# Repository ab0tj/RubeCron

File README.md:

This is just a goofy SBC I created for myself that is also a binary clock.
I have made it public in case it is helpful to anyone else, but it isn't intended to be finished product by any means.

That said, it works for me but YMMV.

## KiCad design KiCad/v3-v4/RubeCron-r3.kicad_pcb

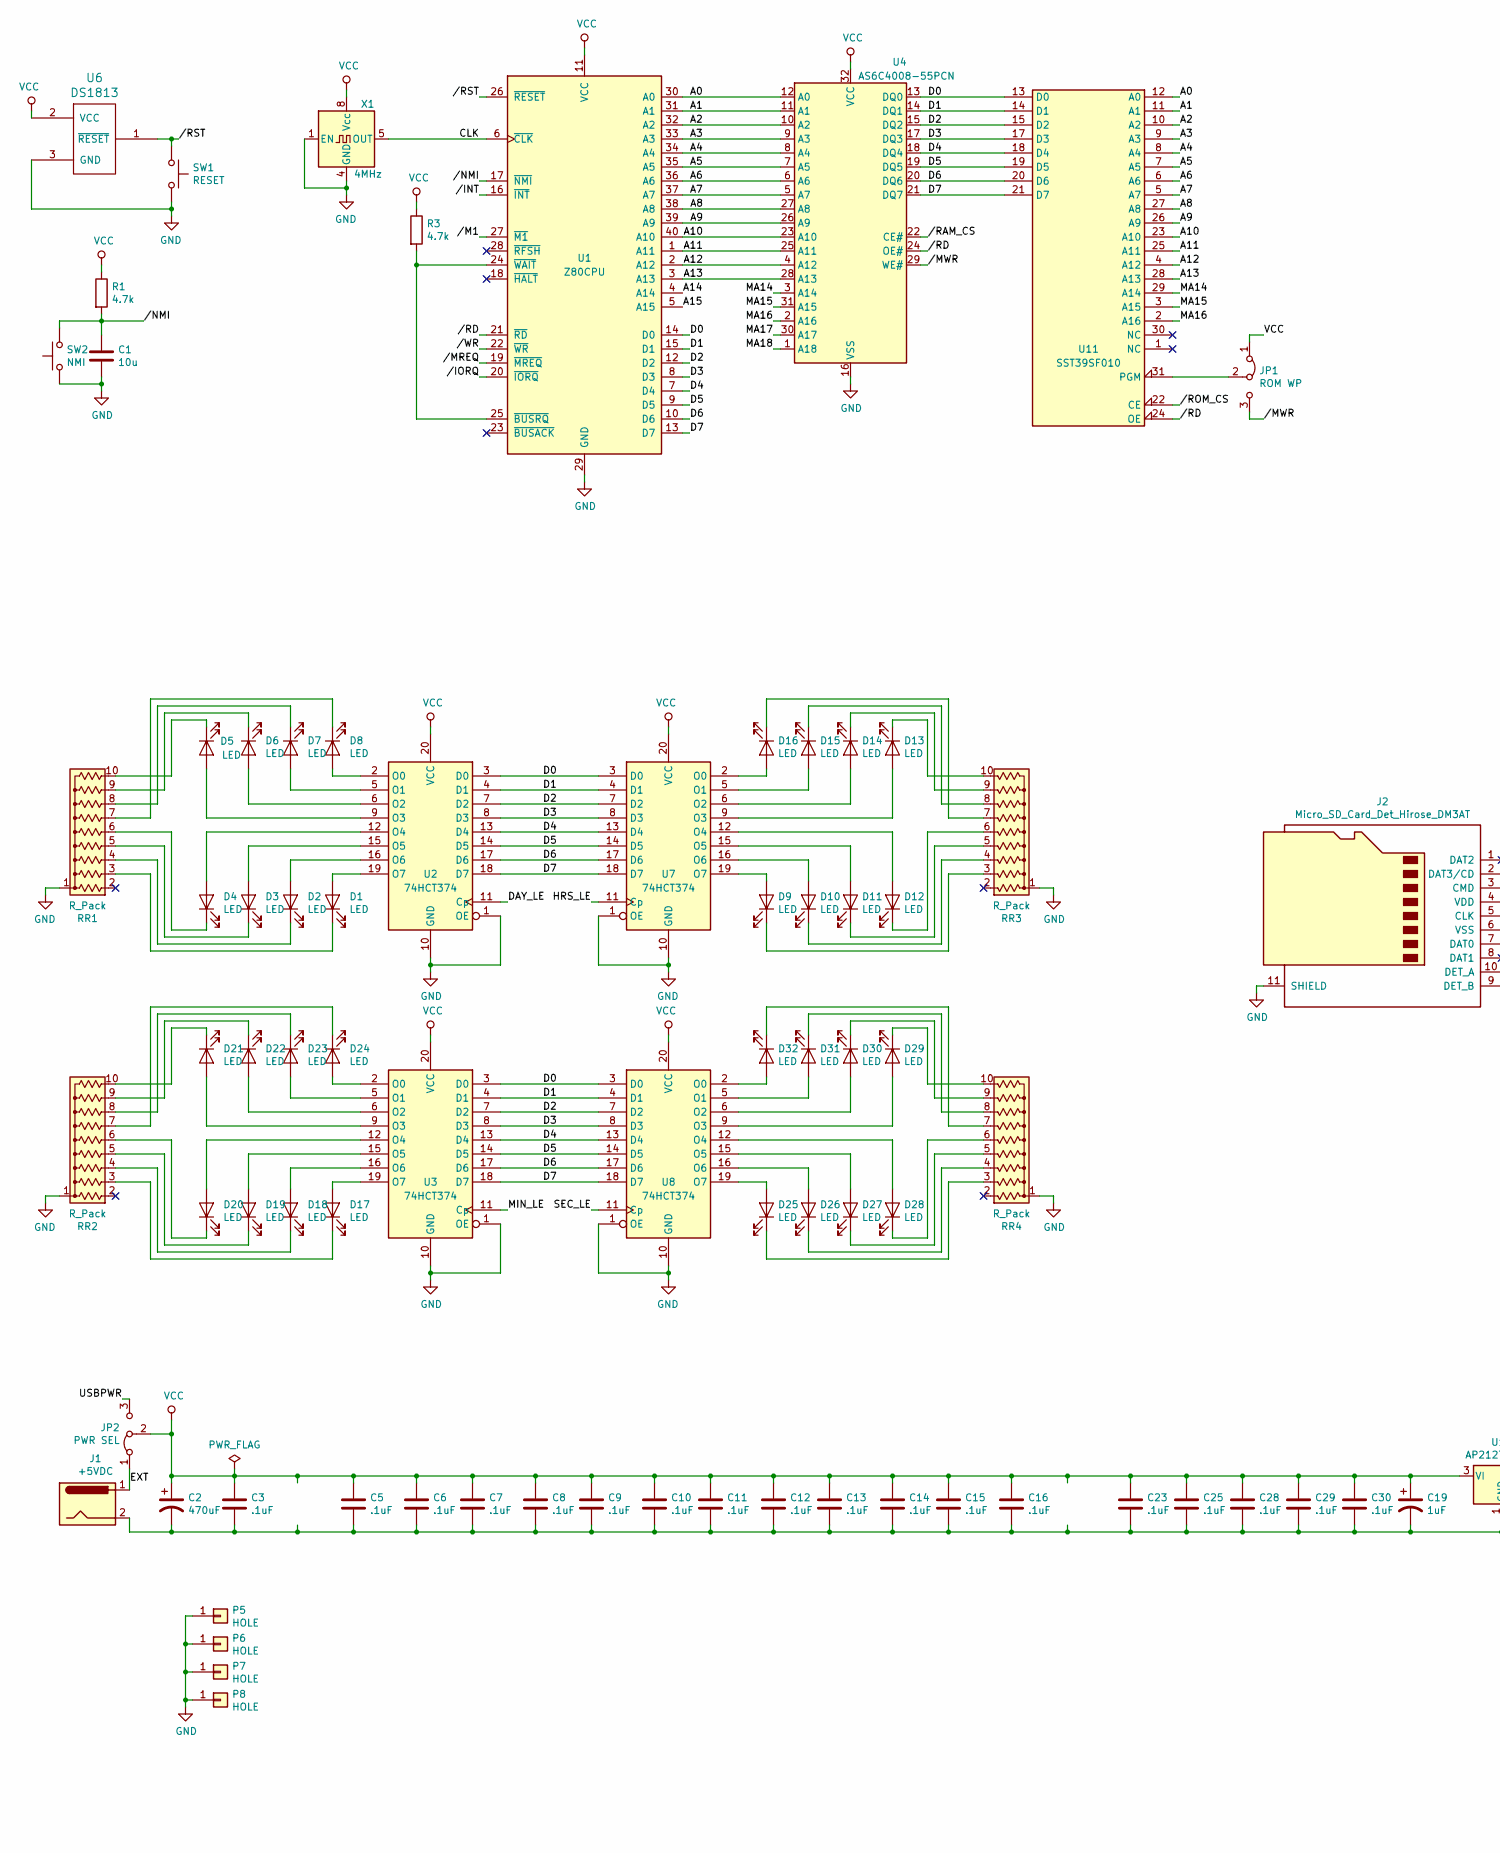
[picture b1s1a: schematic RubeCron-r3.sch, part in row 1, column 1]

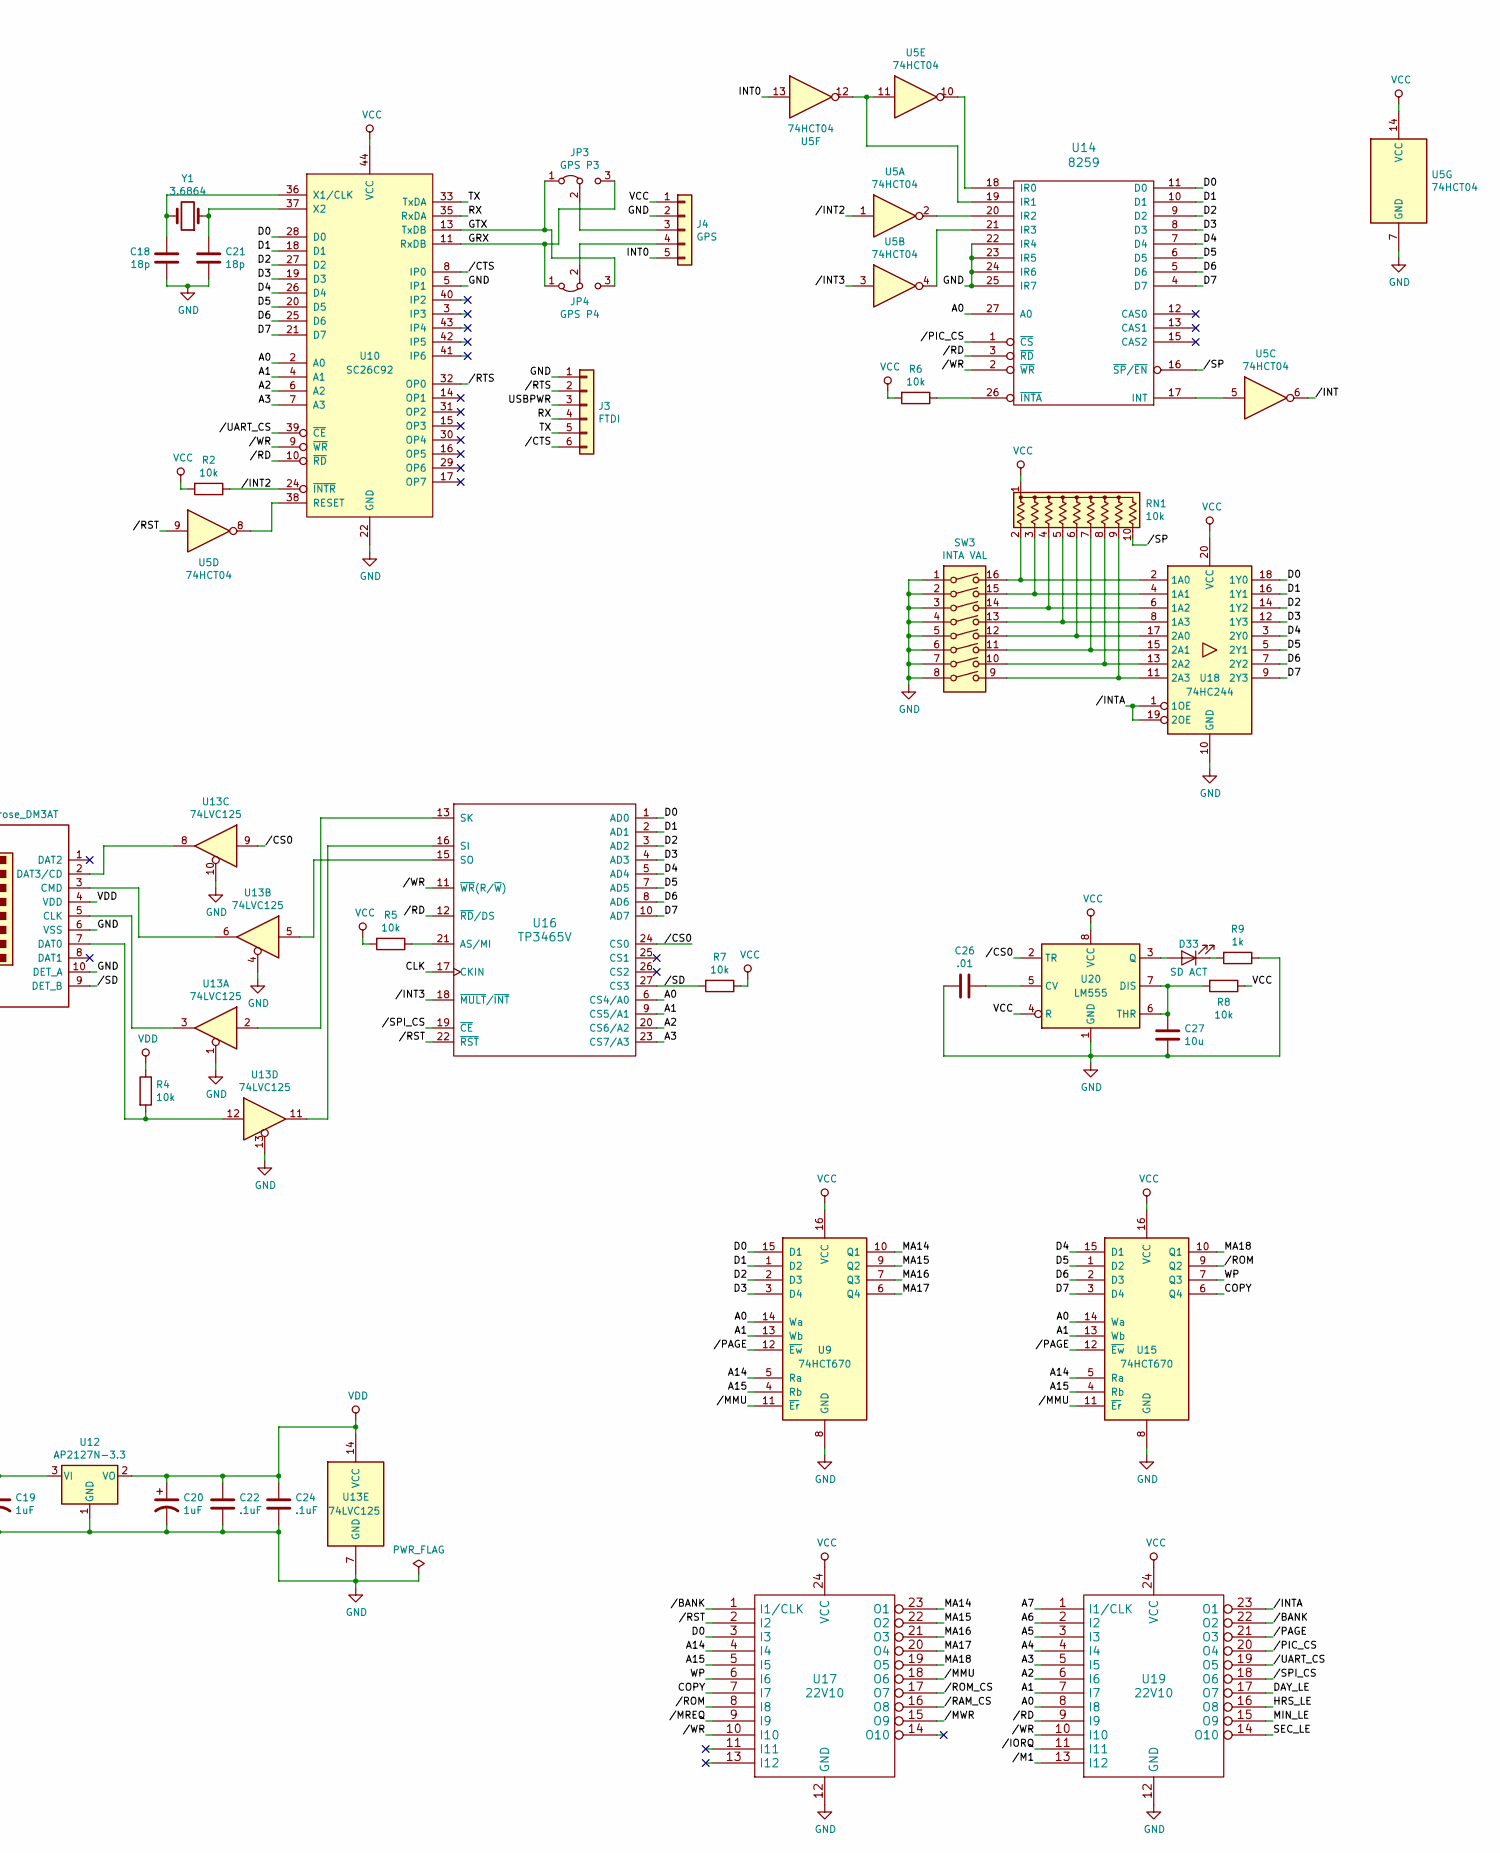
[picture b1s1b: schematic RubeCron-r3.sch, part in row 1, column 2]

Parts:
C1, C27: 10u; C_Disc_D5.0mm_W2.5mm_P5.00mm
C2: 470uF; CP_Radial_D8.0mm_P3.50mm
C3, C5, C6, C7, C8, C9, C10, C11, C12, C13, C14, C15, C16, C23, C25, C28, C29, C30: .1uF; C_Disc_D5.0mm_W2.5mm_P5.00mm
C18, C21: 18p; C_Disc_D5.0mm_W2.5mm_P5.00mm
C19, C20: 1uF; C_0805_2012Metric_Pad1.15x1.40mm_HandSolder
C22, C24: .1uF; C_0805_2012Metric_Pad1.15x1.40mm_HandSolder
C26: .01; C_Disc_D5.0mm_W2.5mm_P5.00mm
D1, D2, D3, D4, D5, D6, D7, D8, D9, D10, D11, D12, D13, D14, D15, D16, D17, D18, D19, D20, D21, D22, D23, D24, D25, D26, D27, D28, D29, D30, D31, D32: LED; LED_D5.0mm
D33: SD ACT; LED_D3.0mm
J1: +5VDC; BarrelJack_CUI_PJ-102AH_Horizontal
J2: Micro_SD_Card_Det_Hirose_DM3AT; microSD_HC_Hirose_DM3AT-SF-PEJM5
J3: FTDI; PinHeader_1x06_P2.54mm_Horizontal
J4: GPS; PinSocket_1x05_P2.54mm_Vertical
JP1: ROM WP; PinHeader_1x03_P2.54mm_Vertical
JP2: PWR SEL; PinHeader_1x03_P2.54mm_Vertical
JP3: GPS P3; SolderJumper-3_P1.3mm_Open_Pad1.0x1.5mm
JP4: GPS P4; SolderJumper-3_P1.3mm_Open_Pad1.0x1.5mm
P5, P6, P7, P8: HOLE; MountingHole_3mm_Pad
R1, R3: 4.7k; R_Axial_DIN0207_L6.3mm_D2.5mm_P7.62mm_Horizontal
R2, R5, R6, R7, R8: 10k; R_Axial_DIN0207_L6.3mm_D2.5mm_P7.62mm_Horizontal
R4: 10k; R_0805_2012Metric_Pad1.15x1.40mm_HandSolder
R9: 1k; R_Axial_DIN0207_L6.3mm_D2.5mm_P7.62mm_Horizontal
RN1: 10k; R_Array_SIP10
RR1, RR2, RR3, RR4: R_Pack; R_Array_SIP10
SW1: RESET; SW_PUSH_6mm
SW2: NMI; SW_PUSH_6mm
SW3: INTA VAL; SW_DIP_SPSTx08_Slide_9.78x22.5mm_W7.62mm_P2.54mm
U1: Z80CPU; DIP-40_W15.24mm_Socket
U2, U3, U7, U8: 74HCT374; DIP-20_W7.62mm_Socket
U4: AS6C4008-55PCN; DIP-32_W15.24mm_Socket
U5: 74HCT04; DIP-14_W7.62mm_Socket
U6: DS1813; TO-92L_Inline
U9, U15: 74HCT670; DIP-16_W7.62mm_Socket
U10: SC26C92; PLCC-44_THT-Socket
U11: SST39SF010; DIP-32_W15.24mm_Socket
U12: AP2127N-3.3; SOT-23
U13: 74LVC125; SOIC-14_3.9x8.7mm_P1.27mm
U14: 8259; PLCC-28_THT-Socket
U16: TP3465V; PLCC-28_THT-Socket
U17, U19: 22V10; DIP-24_W7.62mm_Socket
U18: 74HC244; DIP-20_W7.62mm_Socket
U20: LM555; DIP-8_W7.62mm_Socket
X1: 4MHz; Oscillator_DIP-8
Y1: 3.6864; Crystal_HC49-U_Vertical

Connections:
//BANK: U17.1 (I1/CLK), U19.22 (O2)
//CS0: U13.9, U16.24 (CS0), U20.2 (TR)
//CTS: J3.6, U10.8 (IP0)
//INT: U1.16 (~INT~), U5.6
//INT2: R2.1, U5.1, U10.24 (~INTR)
//INT3: U5.3, U16.18 (~MULT~/~INT)
//INTA: U18.1 (1OE), U18.19 (2OE), U19.23 (O1)
//IORQ: U1.20 (~IORQ~), U19.11 (I11)
//M1: U1.27 (~M1~), U19.13 (I12)
//MMU: U9.11 (~Er), U15.11 (~Er), U17.18 (O6)
//MREQ: U1.19 (~MREQ~), U17.9 (I9)
//MWR: JP1.3 (B), U4.29 (WE#), U17.15 (O9)
//NMI: C1.1, R1.2, SW2.2, U1.17 (~NMI~)
//PAGE: U9.12 (~Ew), U15.12 (~Ew), U19.21 (O3)
//PIC_CS: U14.1 (~CS), U19.20 (O4)
//RAM_CS: U4.22 (CE#), U17.16 (O8)
//RD: U1.21 (~RD~), U4.24 (OE#), U10.10 (~RD), U11.24 (OE), U14.3 (~RD), U16.12 (~RD~/DS), U19.9 (I9)
//ROM: U15.9 (Q2), U17.8 (I8)
//ROM_CS: U11.22 (CE), U17.17 (O7)
//RST: SW1.2, U1.26 (~RESET~), U5.9, U6.1 (~RESET), U16.22 (~RST), U17.2 (I2)
//RTS: J3.2, U10.32 (OP0)
//SD: J2.9 (DET_B), R7.2, U16.27 (CS3)
//SP: RN1.10 (R9), U14.16 (~SP~/~EN~)
//SPI_CS: U16.19 (~CE), U19.18 (O6)
//UART_CS: U10.39 (~CE), U19.19 (O5)
//WR: U1.22 (~WR~), U10.9 (~WR), U14.2 (~WR), U16.11 (~WR~(R/~W~)), U17.10 (I10), U19.10 (I10)
/A0: U1.30 (A0), U4.12 (A0), U9.14 (Wa), U10.2 (A0), U11.12 (A0), U14.27 (A0), U15.14 (Wa), U16.6 (CS4/A0), U19.8 (I8)
/A1: U1.31 (A1), U4.11 (A1), U9.13 (Wb), U10.4 (A1), U11.11 (A1), U15.13 (Wb), U16.9 (CS5/A1), U19.7 (I7)
/A2: U1.32 (A2), U4.10 (A2), U10.6 (A2), U11.10 (A2), U16.20 (CS6/A2), U19.6 (I6)
/A3: U1.33 (A3), U4.9 (A3), U10.7 (A3), U11.9 (A3), U16.23 (CS7/A3), U19.5 (I5)
/A4: U1.34 (A4), U4.8 (A4), U11.8 (A4), U19.4 (I4)
/A5: U1.35 (A5), U4.7 (A5), U11.7 (A5), U19.3 (I3)
/A6: U1.36 (A6), U4.6 (A6), U11.6 (A6), U19.2 (I2)
/A7: U1.37 (A7), U4.5 (A7), U11.5 (A7), U19.1 (I1/CLK)
/A8: U1.38 (A8), U4.27 (A8), U11.27 (A8)
/A9: U1.39 (A9), U4.26 (A9), U11.26 (A9)
/A10: U1.40 (A10), U4.23 (A10), U11.23 (A10)
/A11: U1.1 (A11), U4.25 (A11), U11.25 (A11)
/A12: U1.2 (A12), U4.4 (A12), U11.4 (A12)
/A13: U1.3 (A13), U4.28 (A13), U11.28 (A13)
/A14: U1.4 (A14), U9.5 (Ra), U15.5 (Ra), U17.4 (I4)
/A15: U1.5 (A15), U9.4 (Rb), U15.4 (Rb), U17.5 (I5)
/CLK: U1.6 (~CLK~), U16.17 (CKIN), X1.5 (OUT)
/COPY: U15.6 (Q4), U17.7 (I7)
/D0: U1.14 (D0), U2.3 (D0), U3.3 (D0), U4.13 (DQ0), U7.3 (D0), U8.3 (D0), U9.15 (D1), U10.28 (D0), U11.13 (D0), U14.11 (D0), U16.1 (AD0), U17.3 (I3), U18.18 (1Y0)
/D1: U1.15 (D1), U2.4 (D1), U3.4 (D1), U4.14 (DQ1), U7.4 (D1), U8.4 (D1), U9.1 (D2), U10.18 (D1), U11.14 (D1), U14.10 (D1), U16.2 (AD1), U18.16 (1Y1)
/D2: U1.12 (D2), U2.7 (D2), U3.7 (D2), U4.15 (DQ2), U7.7 (D2), U8.7 (D2), U9.2 (D3), U10.27 (D2), U11.15 (D2), U14.9 (D2), U16.3 (AD2), U18.14 (1Y2)
/D3: U1.8 (D3), U2.8 (D3), U3.8 (D3), U4.17 (DQ3), U7.8 (D3), U8.8 (D3), U9.3 (D4), U10.19 (D3), U11.17 (D3), U14.8 (D3), U16.4 (AD3), U18.12 (1Y3)
/D4: U1.7 (D4), U2.13 (D4), U3.13 (D4), U4.18 (DQ4), U7.13 (D4), U8.13 (D4), U10.26 (D4), U11.18 (D4), U14.7 (D4), U15.15 (D1), U16.5 (AD4), U18.3 (2Y0)
/D5: U1.9 (D5), U2.14 (D5), U3.14 (D5), U4.19 (DQ5), U7.14 (D5), U8.14 (D5), U10.20 (D5), U11.19 (D5), U14.6 (D5), U15.1 (D2), U16.7 (AD5), U18.5 (2Y1)
/D6: U1.10 (D6), U2.17 (D6), U3.17 (D6), U4.20 (DQ6), U7.17 (D6), U8.17 (D6), U10.25 (D6), U11.20 (D6), U14.5 (D6), U15.2 (D3), U16.8 (AD6), U18.7 (2Y2)
/D7: U1.13 (D7), U2.18 (D7), U3.18 (D7), U4.21 (DQ7), U7.18 (D7), U8.18 (D7), U10.21 (D7), U11.21 (D7), U14.4 (D7), U15.3 (D4), U16.10 (AD7), U18.9 (2Y3)
/DAY_LE: U2.11 (Cp), U19.17 (O7)
/EXT: J1.1, JP2.1 (A)
/GRX: JP3.3 (B), JP4.1 (A), U10.11 (RxDB)
/GTX: JP3.1 (A), JP4.3 (B), U10.13 (TxDB)
/HRS_LE: U7.11 (Cp), U19.16 (O8)
/INT0: J4.5, U5.13
/MA14: U4.3 (A14), U9.10 (Q1), U11.29 (A14), U17.23 (O1)
/MA15: U4.31 (A15), U9.9 (Q2), U11.3 (A15), U17.22 (O2)
/MA16: U4.2 (A16), U9.7 (Q3), U11.2 (A16), U17.21 (O3)
/MA17: U4.30 (A17), U9.6 (Q4), U17.20 (O4)
/MA18: U4.1 (A18), U15.10 (Q1), U17.19 (O5)
/MIN_LE: U3.11 (Cp), U19.15 (O9)
/RX: J3.4, U10.35 (RxDA)
/SEC_LE: U8.11 (Cp), U19.14 (O10)
/TX: J3.5, U10.33 (TxDA)
/USBPWR: J3.3, JP2.3 (B)
/WP: U15.7 (Q3), U17.6 (I6)
GND: C1.2, C2.2, C3.2, C5.2, C6.2, C7.2, C8.2, C9.2, C10.2, C11.2, C12.2, C13.2, C14.2, C15.2, C16.2, C18.2, C19.2, C20.2, C21.2, C22.2, C23.2, C24.2, C25.2, C26.2, C27.2, C28.2, C29.2, C30.2, J1.2, J2.6 (VSS), J2.10 (DET_A), J2.11 (SHIELD), J3.1, J4.2, P5.1, P6.1, P7.1, P8.1, R9.1, RR1.1 (common), RR2.1 (common), RR3.1 (common), RR4.1 (common), SW1.1, SW2.1, SW3.1, SW3.2, SW3.3, SW3.4, SW3.5, SW3.6, SW3.7, SW3.8, U1.29 (GND), U2.1 (OE), U2.10 (GND), U3.1 (OE), U3.10 (GND), U4.16 (VSS), U5.7 (GND), U6.3 (GND), U7.1 (OE), U7.10 (GND), U8.1 (OE), U8.10 (GND), U9.8 (GND), U10.5 (IP1), U10.22 (GND), U11.16 (GND), U12.1 (GND), U13.1, U13.4, U13.7 (GND), U13.10, U13.13, U14.14 (GND), U14.22 (IR4), U14.23 (IR5), U14.24 (IR6), U14.25 (IR7), U15.8 (GND), U16.14 (GND), U17.12 (GND), U18.10 (GND), U19.12 (GND), U20.1 (GND), X1.1 (EN), X1.4 (GND)
unnamed: C18.1, U10.36 (X1/CLK), Y1.2
unnamed: C21.1, U10.37 (X2), Y1.1
unnamed: C26.1, U20.5 (CV)
unnamed: C27.1, R8.2, U20.6 (THR), U20.7 (DIS)
unnamed: D1.1 (K), RR1.3 (R2)
unnamed: D1.2 (A), U2.19 (O7)
unnamed: D2.1 (K), RR1.4 (R3)
unnamed: D2.2 (A), U2.16 (O6)
unnamed: D3.1 (K), RR1.5 (R4)
unnamed: D3.2 (A), U2.15 (O5)
unnamed: D4.1 (K), RR1.6 (R5)
unnamed: D4.2 (A), U2.12 (O4)
unnamed: D5.1 (K), RR1.10 (R9)
unnamed: D5.2 (A), U2.9 (O3)
unnamed: D6.1 (K), RR1.9 (R8)
unnamed: D6.2 (A), U2.6 (O2)
unnamed: D7.1 (K), RR1.8 (R7)
unnamed: D7.2 (A), U2.5 (O1)
unnamed: D8.1 (K), RR1.7 (R6)
unnamed: D8.2 (A), U2.2 (O0)
unnamed: D9.1 (K), RR3.3 (R2)
unnamed: D9.2 (A), U7.19 (O7)
unnamed: D10.1 (K), RR3.4 (R3)
unnamed: D10.2 (A), U7.16 (O6)
unnamed: D11.1 (K), RR3.5 (R4)
unnamed: D11.2 (A), U7.15 (O5)
unnamed: D12.1 (K), RR3.6 (R5)
unnamed: D12.2 (A), U7.12 (O4)
unnamed: D13.1 (K), RR3.10 (R9)
unnamed: D13.2 (A), U7.9 (O3)
unnamed: D14.1 (K), RR3.9 (R8)
unnamed: D14.2 (A), U7.6 (O2)
unnamed: D15.1 (K), RR3.8 (R7)
unnamed: D15.2 (A), U7.5 (O1)
unnamed: D16.1 (K), RR3.7 (R6)
unnamed: D16.2 (A), U7.2 (O0)
unnamed: D17.1 (K), RR2.3 (R2)
unnamed: D17.2 (A), U3.19 (O7)
unnamed: D18.1 (K), RR2.4 (R3)
unnamed: D18.2 (A), U3.16 (O6)
unnamed: D19.1 (K), RR2.5 (R4)
unnamed: D19.2 (A), U3.15 (O5)
unnamed: D20.1 (K), RR2.6 (R5)
unnamed: D20.2 (A), U3.12 (O4)
unnamed: D21.1 (K), RR2.10 (R9)
unnamed: D21.2 (A), U3.9 (O3)
unnamed: D22.1 (K), RR2.9 (R8)
unnamed: D22.2 (A), U3.6 (O2)
unnamed: D23.1 (K), RR2.8 (R7)
unnamed: D23.2 (A), U3.5 (O1)
unnamed: D24.1 (K), RR2.7 (R6)
unnamed: D24.2 (A), U3.2 (O0)
unnamed: D25.1 (K), RR4.3 (R2)
unnamed: D25.2 (A), U8.19 (O7)
unnamed: D26.1 (K), RR4.4 (R3)
unnamed: D26.2 (A), U8.16 (O6)
unnamed: D27.1 (K), RR4.5 (R4)
unnamed: D27.2 (A), U8.15 (O5)
unnamed: D28.1 (K), RR4.6 (R5)
unnamed: D28.2 (A), U8.12 (O4)
unnamed: D29.1 (K), RR4.10 (R9)
unnamed: D29.2 (A), U8.9 (O3)
unnamed: D30.1 (K), RR4.9 (R8)
unnamed: D30.2 (A), U8.6 (O2)
unnamed: D31.1 (K), RR4.8 (R7)
unnamed: D31.2 (A), U8.5 (O1)
unnamed: D32.1 (K), RR4.7 (R6)
unnamed: D32.2 (A), U8.2 (O0)
unnamed: D33.1 (K), R9.2
unnamed: D33.2 (A), U20.3 (Q)
unnamed: J2.2 (DAT3/CD), U13.8
unnamed: J2.3 (CMD), U13.6
unnamed: J2.5 (CLK), U13.3
unnamed: J2.7 (DAT0), R4.2, U13.12
unnamed: J4.3, JP3.2 (C)
unnamed: J4.4, JP4.2 (C)
unnamed: JP1.2 (C), U11.31 (PGM)
unnamed: R3.2, U1.24 (~WAIT~), U1.25 (~BUSRQ~)
unnamed: R5.1, U16.21 (AS/MI)
unnamed: R6.1, U14.26 (~INTA)
unnamed: RN1.2 (R1), SW3.16, U18.2 (1A0)
unnamed: RN1.3 (R2), SW3.15, U18.4 (1A1)
unnamed: RN1.4 (R3), SW3.14, U18.6 (1A2)
unnamed: RN1.5 (R4), SW3.13, U18.8 (1A3)
unnamed: RN1.6 (R5), SW3.12, U18.17 (2A0)
unnamed: RN1.7 (R6), SW3.11, U18.15 (2A1)
unnamed: RN1.8 (R7), SW3.10, U18.13 (2A2)
unnamed: RN1.9 (R8), SW3.9, U18.11 (2A3)
unnamed: U5.8, U10.38 (RESET)
unnamed: U13.2, U16.13 (SK)
unnamed: U13.5, U16.15 (SO)
unnamed: U13.11, U16.16 (SI)
unnamed: U5.5, U14.17 (INT)
unnamed: U5.10, U14.18 (IR0)
unnamed: U5.11, U5.12, U14.19 (IR1)
unnamed: U5.2, U14.20 (IR2)
unnamed: U5.4, U14.21 (IR3)
VCC: C2.1, C3.1, C5.1, C6.1, C7.1, C8.1, C9.1, C10.1, C11.1, C12.1, C13.1, C14.1, C15.1, C16.1, C19.1, C23.1, C25.1, C28.1, C29.1, C30.1, J4.1, JP1.1 (A), JP2.2 (C), R1.1, R2.2, R3.1, R5.2, R6.2, R7.1, R8.1, RN1.1 (common), U1.11 (VCC), U2.20 (VCC), U3.20 (VCC), U4.32 (VCC), U5.14 (VCC), U6.2 (VCC), U7.20 (VCC), U8.20 (VCC), U9.16 (VCC), U10.44 (VCC), U11.32 (VCC), U12.3 (VI), U14.28 (VCC), U15.16 (VCC), U16.28 (VCC), U17.24 (VCC), U18.20 (VCC), U19.24 (VCC), U20.4 (R), U20.8 (VCC), X1.8 (Vcc)
VDD: C20.1, C22.1, C24.1, J2.4 (VDD), R4.1, U12.2 (VO), U13.14 (VCC)

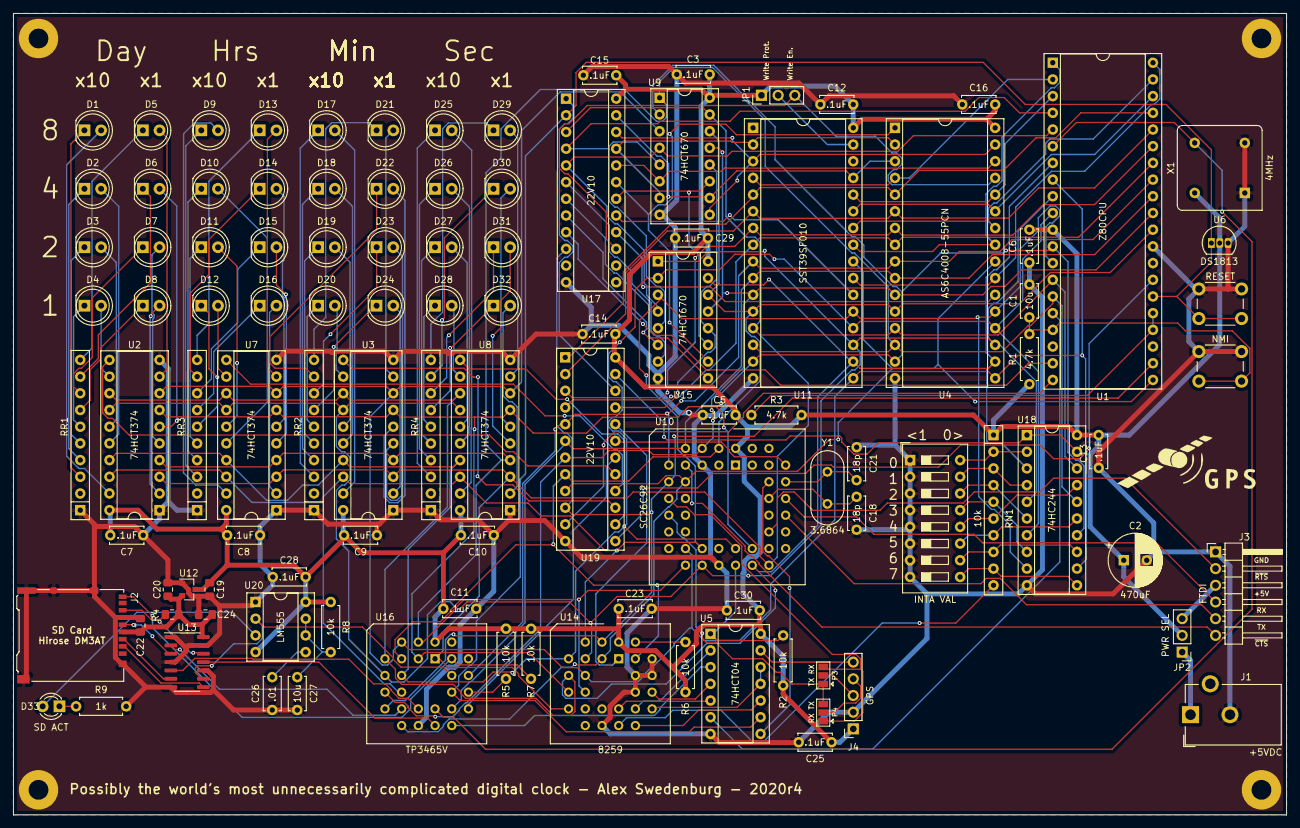
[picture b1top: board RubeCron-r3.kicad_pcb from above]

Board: 2 copper layers, 193.7 x 121.9 mm, 114 parts (1 on the bottom side), 169 nets.

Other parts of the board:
G2: LOGO; GPSLOGO
G3: LOGO; MRSPARLKE2

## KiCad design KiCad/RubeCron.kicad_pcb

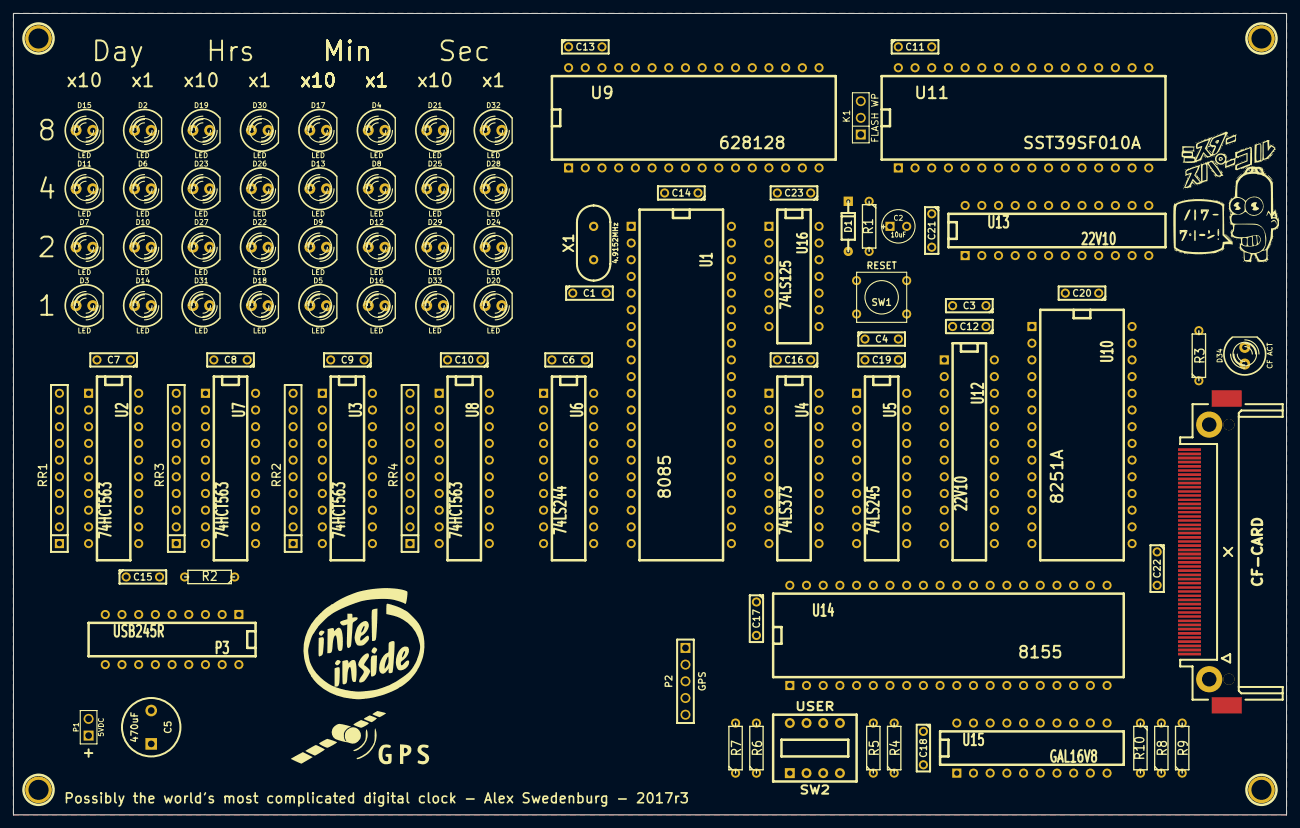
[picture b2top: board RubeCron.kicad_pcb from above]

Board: 2 copper layers, 193.7 x 121.9 mm, 102 parts (0 on the bottom side), 177 nets, no tracks yet.

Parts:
C1: 20pF; C2
C2: 10uF; C1V5
C3, C4, C6, C7, C8, C9, C10, C11, C12, C13, C14, C15, C16, C17, C18, C19, C20, C21, C22, C23: .1uF; C2
C5: 470uF; C2V8
CON1: CF-CARD; 3M-N7E50-Short-NonInv
D1: 1N4148; DO-35
D2, D3, D4, D5, D6, D7, D8, D9, D10, D11, D12, D13, D14, D15, D16, D17, D18, D19, D20, D21, D22, D23, D24, D25, D26, D27, D28, D29, D30, D31, D32, D33: LED; LED-5MM
D34: CF ACT; LED-5MM
G1: LOGO; INTEL
G2: LOGO; GPSLOGO
G3: LOGO; MRSPARLKE2
K1: FLASH WP; PIN_ARRAY_3X1
P1: 5VDC; PIN_ARRAY_2X1
P2: GPS; PIN_ARRAY_5x1
P3: USB245R; DIP-18__300
P5, P6, P7, P8: CONN_1; 1pin
R1: 100k; R3
R2: 10k; R3
R3: 470; R3
R4, R5, R6, R7: 4.7k; R3
R8, R9, R10: 1000; R3
RR1, RR2, RR3, RR4: 470; r_pack9
SW1: RESET; SW_PUSH_SMALL
SW2: USER; SWDIP4
U1: 8085; DIP-40__600
U2, U3, U7, U8: 74HCT563; DIP-20__300
U4: 74LS373; DIP-20__300
U5: 74LS245; DIP-20__300
U6: 74LS244; DIP-20__300
U9: 628128; DIP-32__600
U10: 8251A; DIP-28__600
U11: SST39SF010A; DIP-32__600
U12, U13: 22V10; DIP-24__300
U14: 8155; DIP-40__600
U15: GAL16V8; DIP-20__300
U16: 74LS125; DIP-14__300
X1: 4.9152MHz; HC-49V

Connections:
/A0: U4.2, U9.12, U10.12, U11.12, U12.1
/A1: U4.5, U9.11, U11.11, U12.2
/A2: U4.6, U9.10, U11.10, U12.3
/A3: U4.9, U9.9, U11.9, U12.4
/A4: U4.12, U9.8, U11.8, U12.5
/A5: U4.15, U9.7, U11.7, U12.6
/A6: U4.16, U9.6, U11.6, U12.7
/A7: U4.19, U9.5, U11.5, U12.8
/A8: U1.21, U9.27, U11.27
/A9: U1.22, U9.26, U11.26
/A10: U1.23, U9.23, U11.23
/A11: U1.24, U9.25, U11.25
/A12: U1.25, U9.4, U11.4
/A13: U1.26, U9.28, U11.28
/A14: U1.27, U13.6
/A15: U1.28, U13.7
/AD0: U1.12, U4.3, U5.2, U6.2
/AD1: U1.13, U4.4, U5.3, U6.4
/AD2: U1.14, U4.7, U5.4, U6.6
/AD3: U1.15, U4.8, U5.5, U6.8
/AD4: U1.16, U4.13, U5.6, U6.11
/AD5: U1.17, U4.14, U5.7, U6.13
/AD6: U1.18, U4.17, U5.8, U6.15
/AD7: U1.19, U4.18, U5.9, U6.17
/ALE: U1.30, U4.11, U14.11
/BAUD: U10.9, U10.25, U14.6
/BCLK: U10.20, U12.13, U13.13, U14.3, U16.11
/BRESET: U10.21, U13.11, U14.4, U16.6
/CD0: U2.2, U3.2, U6.18, U7.2, U8.2
/CD1: U2.3, U3.3, U6.16, U7.3, U8.3
/CD2: U2.4, U3.4, U6.14, U7.4, U8.4
/CD3: U2.5, U3.5, U6.12, U7.5, U8.5
/CD4: U2.6, U3.6, U6.9, U7.6, U8.6
/CD5: U2.7, U3.7, U6.7, U7.7, U8.7
/CD6: U2.8, U3.8, U6.5, U7.8, U8.8
/CD7: U2.9, U3.9, U6.3, U7.9, U8.9
/CLK: U1.37, U16.12
/D0: P3.18, U5.18, U9.13, U10.27, U11.13, U13.2, U14.12, U15.2
/D1: P3.16, U5.17, U9.14, U10.28, U11.14, U13.3, U14.13, U15.3
/D2: P3.2, U5.16, U9.15, U10.1, U11.15, U13.4, U14.14, U15.4
/D3: P3.5, U5.15, U9.17, U10.2, U11.17, U13.5, U14.15, U15.5
/D4: P3.17, U5.14, U9.18, U10.5, U11.18, U14.16, U15.6
/D5: P3.4, U5.13, U9.19, U10.6, U11.19, U14.17, U15.7
/D6: P3.13, U5.12, U9.20, U10.7, U11.20, U14.18, U15.8
/D7: P3.3, U5.11, U9.21, U10.8, U11.21, U14.19, U15.9
/DAY_LE: U2.11, U12.19
/HRS_LE: U7.11, U12.18
/IDE_A0: CON1.20, U15.19
/IDE_A1: CON1.19, U15.18
/IDE_A2: CON1.18, U15.17
/IDE_D0: CON1.21, U14.21
/IDE_D1: CON1.22, U14.22
/IDE_D2: CON1.23, U14.23
/IDE_D3: CON1.2, U14.24
/IDE_D4: CON1.3, U14.25
/IDE_D5: CON1.4, U14.26
/IDE_D6: CON1.5, U14.27
/IDE_D7: CON1.6, U14.28
/IDE_D8: CON1.47, U14.29
/IDE_D9: CON1.48, U14.30
/IDE_D10: CON1.49, U14.31
/IDE_D11: CON1.27, U14.32
/IDE_D12: CON1.28, U14.33
/IDE_D13: CON1.29, U14.34
/IDE_D14: CON1.30, U14.35
/IDE_D15: CON1.31, U14.36
/INT0: P2.5, U1.7
/INT1: U1.8, U10.14
/INT2: CON1.37, U1.9
/IO/~M: U1.34, U12.9, U13.8
/MEM_A14: U9.3, U11.29, U13.21
/MEM_A15: U9.31, U11.3, U13.20
/MEM_A16: U9.2, U11.2, U13.19
/MIN_LE: U3.11, U12.17
/RESET: U1.3, U16.5
/SEC_LE: U8.11, U12.16
/~8155_CS: U12.23, U14.8
/~BNKSEL: U12.15, U13.1
/~BRD: U9.24, U10.13, U11.24, U12.10, U13.9, U14.9, U16.3
/~BWR: K1.1, U9.29, U10.10, U12.11, U13.10, U14.10, U16.8
/~IDE_CS0: CON1.7, U15.16
/~IDE_CS1: CON1.32, U15.15
/~IDE_DIOR: CON1.34, U15.13
/~IDE_DIOW: CON1.35, U15.14
/~IDE_RST: CON1.41, U15.12
/~RAM_CS: U9.22, U13.23
/~RD: U1.32, U5.1, U16.2
/~ROM_CS: U11.22, U13.22
/~UART_CS: U10.11, U12.22
/~USB_RD: P3.11, U12.20
/~USB_WR: P3.12, U12.21
/~WR: U1.31, U16.9
GND: C1.2, C2.2, C4.2, C5.2, C6.2, C7.2, C8.2, C9.2, C10.2, C11.2, C12.2, C13.2, C14.2, C15.2, C16.2, C17.2, C18.2, C19.2, C20.2, C21.2, C22.2, C23.2, CON1.1, CON1.8, CON1.9, CON1.10, CON1.11, CON1.12, CON1.14, CON1.15, CON1.16, CON1.17, CON1.39, CON1.50, P1.2, P2.2, P3.1, P3.10, P5.1, P6.1, P7.1, P8.1, SW1.1, SW2.1, SW2.2, SW2.3, SW2.4, U1.5, U1.6, U1.10, U1.20, U1.39, U2.1, U2.10, U3.1, U3.10, U4.1, U4.10, U5.10, U5.19, U6.1, U6.10, U6.19, U7.1, U7.10, U8.1, U8.10, U9.16, U10.4, U10.17, U10.22, U11.16, U12.12, U13.12, U14.20, U15.10, U15.11, U16.1, U16.4, U16.7, U16.10, U16.13
unnamed: P2.3, U10.3
unnamed: P2.4, U10.19
unnamed: P3.6, R2.2
unnamed: D10.2, U2.18
unnamed: D6.2, U2.17
unnamed: D2.2, U2.16
unnamed: D15.2, U2.12
unnamed: D11.2, U2.13
unnamed: D7.2, U2.14
unnamed: D3.2, U2.15
unnamed: D14.2, U2.19
unnamed: D16.2, U3.19
unnamed: D12.2, U3.18
unnamed: D8.2, U3.17
unnamed: D4.2, U3.16
unnamed: D17.2, U3.12
unnamed: D13.2, U3.13
unnamed: D9.2, U3.14
unnamed: K1.2, U11.31
unnamed: D5.2, U3.15
unnamed: D24.1, RR4.3
unnamed: D20.1, RR4.2
unnamed: D33.1, RR4.6
unnamed: D29.1, RR4.7
unnamed: D25.1, RR4.8
unnamed: D21.1, RR4.9
unnamed: D18.1, RR3.2
unnamed: D31.1, RR3.6
unnamed: D27.1, RR3.7
unnamed: D23.1, RR3.8
unnamed: D19.1, RR3.9
unnamed: D32.1, RR4.5
unnamed: D28.1, RR4.4
unnamed: D34.2, R3.2
unnamed: D33.2, U8.15
unnamed: D3.1, RR1.6
unnamed: D7.1, RR1.7
unnamed: D29.2, U8.14
unnamed: D11.1, RR1.8
unnamed: D15.1, RR1.9
unnamed: D2.1, RR1.5
unnamed: D6.1, RR1.4
unnamed: D31.2, U7.15
unnamed: D18.2, U7.19
unnamed: D22.2, U7.18
unnamed: D26.2, U7.17
unnamed: D30.2, U7.16
unnamed: D19.2, U7.12
unnamed: D23.2, U7.13
unnamed: D27.2, U7.14
unnamed: D20.2, U8.19
unnamed: D24.2, U8.18
unnamed: D28.2, U8.17
unnamed: D32.2, U8.16
unnamed: D21.2, U8.12
unnamed: D25.2, U8.13
unnamed: D5.1, RR2.6
unnamed: D9.1, RR2.7
unnamed: D13.1, RR2.8
unnamed: D17.1, RR2.9
unnamed: D30.1, RR3.5
unnamed: D26.1, RR3.4
unnamed: D22.1, RR3.3
unnamed: D10.1, RR1.3
unnamed: D14.1, RR1.2
unnamed: D4.1, RR2.5
unnamed: D8.1, RR2.4
unnamed: D12.1, RR2.3
unnamed: D16.1, RR2.2
unnamed: CON1.36, R9.2
unnamed: CON1.45, R3.1
unnamed: CON1.44, R8.2
unnamed: CON1.46, R10.1
unnamed: C2.1, C3.2, C4.1, D1.1, R1.2, SW1.2, U1.36
unnamed: U1.1, X1.2
unnamed: C1.1, U1.2, X1.1
unnamed: U12.14, U15.1
unnamed: R7.2, SW2.8, U14.1
unnamed: P3.14, U14.2
unnamed: P3.15, U14.5
unnamed: R6.2, SW2.7, U14.39
unnamed: R5.2, SW2.6, U14.38
unnamed: R4.2, SW2.5, U14.37
VCC: C3.1, C5.1, C6.1, C7.1, C8.1, C9.1, C10.1, C11.1, C12.1, C13.1, C14.1, C15.1, C16.1, C17.1, C18.1, C19.1, C20.1, C21.1, C22.1, C23.1, CON1.13, CON1.38, D1.2, D34.1, K1.3, P1.1, P2.1, P3.7, P3.8, R1.1, R2.1, R4.1, R5.1, R6.1, R7.1, R8.1, R9.1, R10.2, RR1.1, RR2.1, RR3.1, RR4.1, U1.35, U1.40, U2.20, U3.20, U4.20, U5.20, U6.20, U7.20, U8.20, U9.30, U9.32, U10.26, U11.32, U12.24, U13.24, U14.7, U14.40, U15.20, U16.14

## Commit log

2018-04-02 First push
2021-09-27 Add v4 files
2021-09-27 Removed deleted files from repo
2023-10-06 Fix readme typos
